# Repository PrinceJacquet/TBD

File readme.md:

# The dashboard of the car: TIM-07
* Software used 
    * KiCad v5
    * STM32 Cube IDE v1.3
    * Sublime Text

## Support Sheet for DashBoard development - TDB

### Function to code

* [x]  Led idle
    * [x] while(1) : blink Delay    
    * [x] PWM               

* [ ]  Led: inform on the status of the car__(hardware missing)__
    1. Break
    2. Front Headlight
    3. Back Headlight

* [ ]  CAN Bus Comminication
    - Rx
    - Tx
        
* [ ]  Servo Controller 
    * [x] PWM -- 50Hz  --> 1/20ms  *--untested*
    * [ ] (BASE) Timer to set the Cycle Duty (OFF / Slow incrementation or fast incrementation)
    * [ ] Timer to set the speed : The periode at which the cycle duty increment or decrement 
    * [x] Power the servo-motor ON/OFF

* [x]  Buttons and interruptions
    * Cycle to choose wiper speed
        * Wiper off
        * Wiper Speed 1
        * Wiper speed 2
    * Fan On/Off
    * Front Headlight 
    * Back Headlight
   
## On Hardware
* V1
    * CLIM switch 
    * Wiper push boutons
    * HeadLight Front
    * HeadLight Back
    * Break 
## How to:

### PWM 

- [link to course and tutorials!](https://visualgdb.com/tutorials/arm/stm32/pwm/)
- [link to ST resources on TIMERS](https://www.st.com/content/ccc/resource/training/technical/product_training/c4/1b/56/83/3a/a1/47/64/STM32L4_WDG_TIMERS_GPTIM.pdf/files/STM32L4_WDG_TIMERS_GPTIM.pdf/jcr:content/translations/en.STM32L4_WDG_TIMERS_GPTIM.pdf)
- [link to OpenClassroom course](https://openclassrooms.com/fr/courses/4117396-developpez-en-c-pour-lembarque/4629911-configurez-un-modulateur-de-longueur-d-impulsion)
- [link to Servo-Motor operating principle](https://howtomechatronics.com/how-it-works/how-servo-motors-work-how-to-control-servos-using-arduino/)
#### STM32 Timers HardWare
    * The hardwre is a bunch of separate block that can count from 0 to x
     And trigger events when the timer reach 0, maximum value or a compae value. 
#### What are the steps 
    1. We have to start the timer (so it can count)
        1. Pick the relevant timer and channel 
        2. Configure the following parameters so that the timer count at the frequency you need: T_timer=T_(clock)×prescaler×(autoreload+1)
            * counting mode up or down
            * set the prescaler (PSC)
            * set the period (ARR)
            * set clock division if any (CKD)
            * set repetition if any 
    2. We set the duty cycle
        * Using 
    3. We start the PWM using: HAL Functions from ST
    
### Interruptions 
    * Configure pin in STM32 CUBE MX as GPIO EXTIx
    * Using void EXTIx_y_IRQHandler(void){[[ }]]

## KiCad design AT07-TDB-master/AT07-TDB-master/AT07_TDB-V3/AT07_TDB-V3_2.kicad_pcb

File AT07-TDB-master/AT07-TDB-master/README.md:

# TDB Tim 07

### Fonctions necesseaires 
* Gestion EsGl
* Gestion "Clim"
* Pedale frein

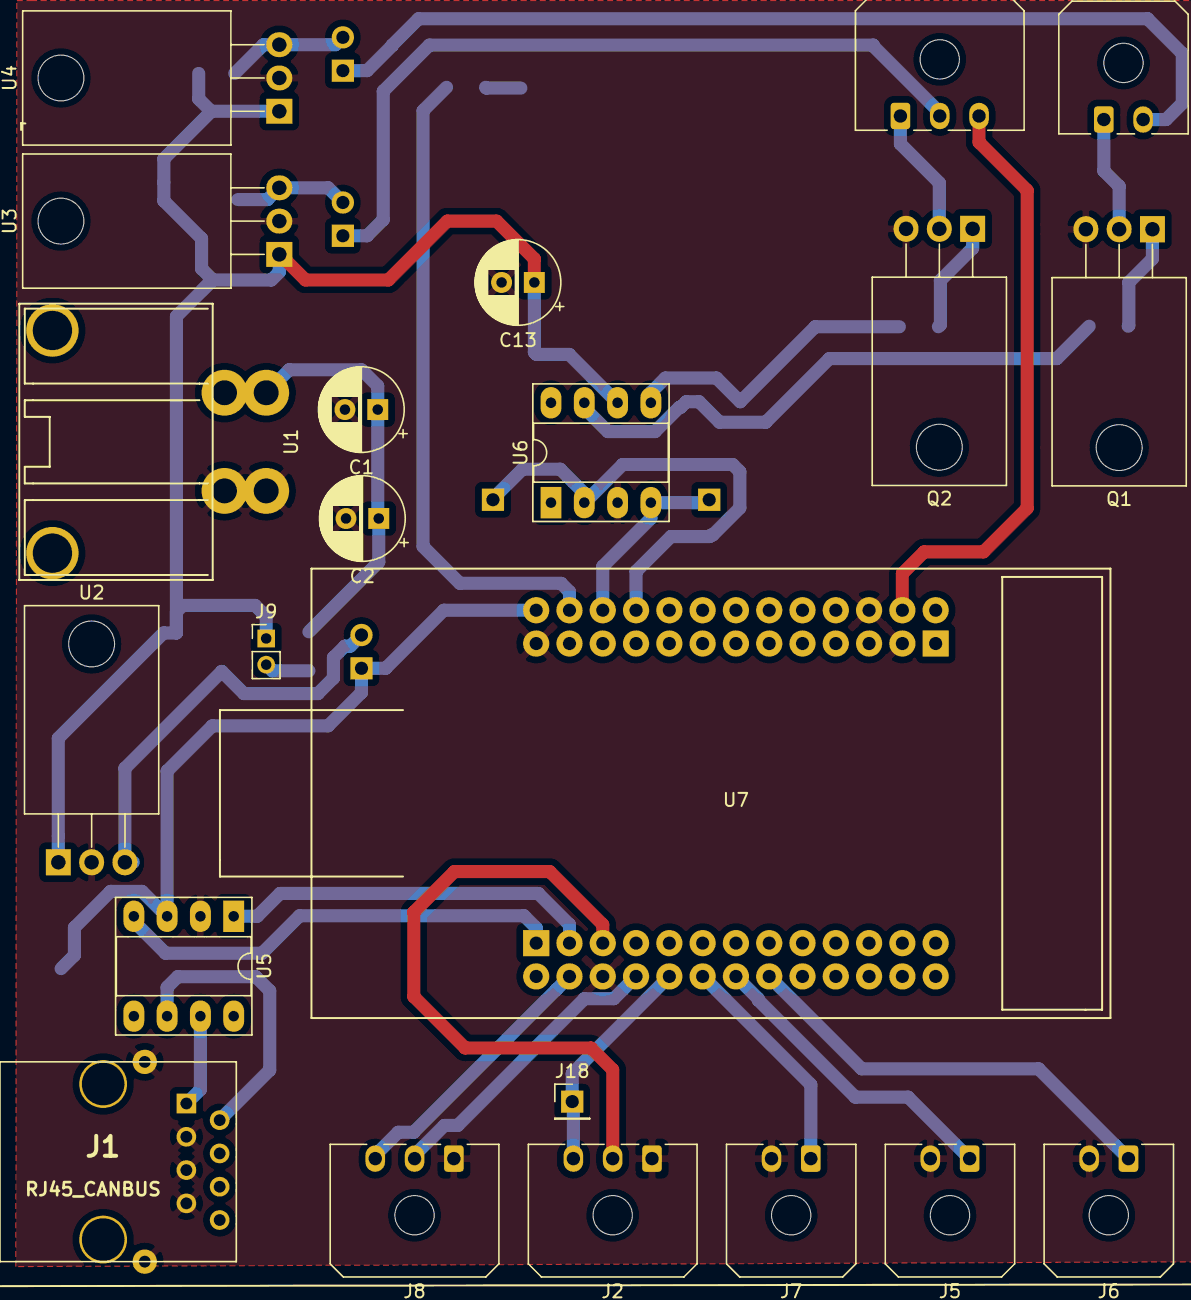
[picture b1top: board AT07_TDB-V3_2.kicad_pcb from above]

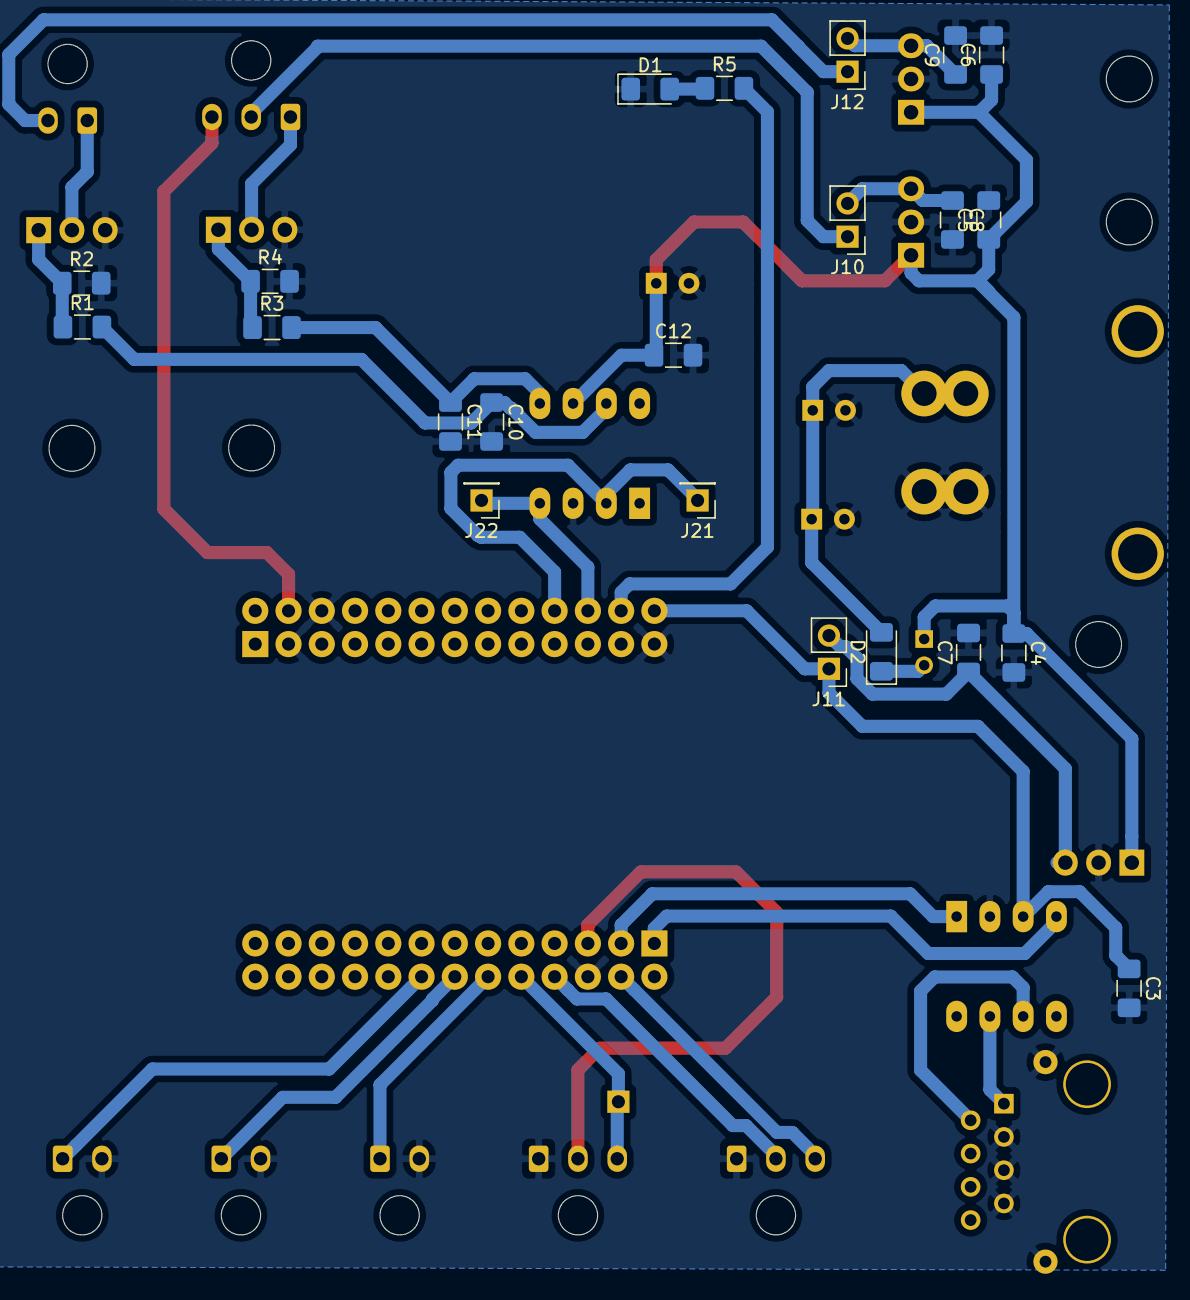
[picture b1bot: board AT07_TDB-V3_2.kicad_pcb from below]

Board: 2 copper layers, 44 parts (22 on the bottom side), 32 nets.

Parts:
C1: 22uF; CP_Radial_D6.3mm_P2.50mm
C2, C13: 1uF; CP_Radial_D6.3mm_P2.50mm
C3, C7, C8, C9, C12: 100nF; C_1206_3216Metric_Pad1.42x1.75mm_HandSolder
C4, C5, C6: 330nF; C_1206_3216Metric_Pad1.42x1.75mm_HandSolder
C10, C11: 1nF; C_1206_3216Metric_Pad1.42x1.75mm_HandSolder
D1: LED; D_1206_3216Metric_Pad1.42x1.75mm_HandSolder
D2: D; D_1206_3216Metric_Pad1.42x1.75mm_HandSolder
J1: RJ45_CANBUS; RJ45_CAN
J2: Conn_01x03_Female_Potar; Molex_Micro-Fit_3.0_43650-0300_1x03_P3.00mm_Horizontal
J3: Conn_01x03_Female_Servomotor; Molex_Micro-Fit_3.0_43650-0300_1x03_P3.00mm_Horizontal
J4, J5, J6, J7: Conn_01x02_Female; Molex_Micro-Fit_3.0_43650-0200_1x02_P3.00mm_Horizontal
J8: Conn_01x03_Female; Molex_Micro-Fit_3.0_43650-0300_1x03_P3.00mm_Horizontal
J9: Conn_01x02_Male; PinHeader_1x02_P2.00mm_Vertical
J10, J11, J12: Conn_01x02_Male; PinHeader_1x02_P2.54mm_Vertical
J18, J21, J22: Conn_01x01_Female; PinHeader_1x01_P2.54mm_Vertical
Q1, Q2: IRFZ44Z; TO-220-3_Horizontal_TabDown
R1, R3: 10; R_1206_3216Metric_Pad1.42x1.75mm_HandSolder
R2, R4: 10k; R_1206_3216Metric_Pad1.42x1.75mm_HandSolder
R5: R; R_1206_3216Metric_Pad1.42x1.75mm_HandSolder
U1: MOLEX_SABRE_46007-1102
U2, U3: L7805; TO-220-3_Horizontal_TabDown
U4: L7812; TO-220-3_Horizontal_TabDown
U5: MCP2551-I-SN; DIP-8_W7.62mm_Socket_LongPads
U6: TC4424; DIP-8_W7.62mm_Socket_LongPads
U7: STM32H103-OlimexBoard

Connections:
+3V3: J2.2, U7.5
+5V: C3.1, J11.1, U5.3, U7.52
+5VA: J3.2, J10.1
+12VA: J4.2, J12.1
+15V: C4.1, C5.1, C6.1, C12.1, C13.1, J9.1, U2.1, U3.1, U4.1, U6.6
BRAKES_SW: J7.1, U7.12
CANH: J1.1, U5.7
CANL: J1.2, U5.6
CANRX: U5.4, U7.1
CANTX: U5.1, U7.3
CLIM_CMD_HPWR: C10.1, R1.2, U6.7
CLIM_CMD_LPWR: J21.1, U6.2, U7.46
CLIM_SW: J5.1, U7.14
GND: C1.2, C2.2, C3.2, C4.2, C5.2, C6.2, C7.2, C8.2, C9.2, C10.2, C11.2, C12.2, C13.2, D1.1, J1.3, J1.5, J1.7, J1.9, J2.1, J5.2, J6.2, J7.2, J8.1, Q1.3, Q2.3, R2.2, R4.2, U1.1, U2.2, U3.2, U4.2, U5.2, U6.3, U7.6, U7.29, U7.32, U7.51
LIGHTS_SW: J6.1, U7.16
unnamed: C1.1, C2.1, D2.2, U1.2
unnamed: C7.1, J11.2, U2.3
unnamed: C8.1, J10.2, U3.3
unnamed: C9.1, J12.2, U4.3
unnamed: D1.2, R5.1
unnamed: D2.1, J9.2
unnamed: J3.1, Q2.2
unnamed: J4.1, Q1.2
unnamed: Q1.1, R1.1, R2.1
unnamed: Q2.1, R3.1, R4.1
unnamed: R5.2, U7.50
PWM_SERVO: J3.3, U7.30
SERVO_CMD_HPWR: C11.1, R3.2, U6.5
SERVO_CMD_LPWR: J22.1, U6.4, U7.48
SIGNAL_POTAR: J2.3, J18.1, U7.10
WIPER_SPEED_1: J8.2, U7.8
WIPER_SPEED_2: J8.3, U7.4

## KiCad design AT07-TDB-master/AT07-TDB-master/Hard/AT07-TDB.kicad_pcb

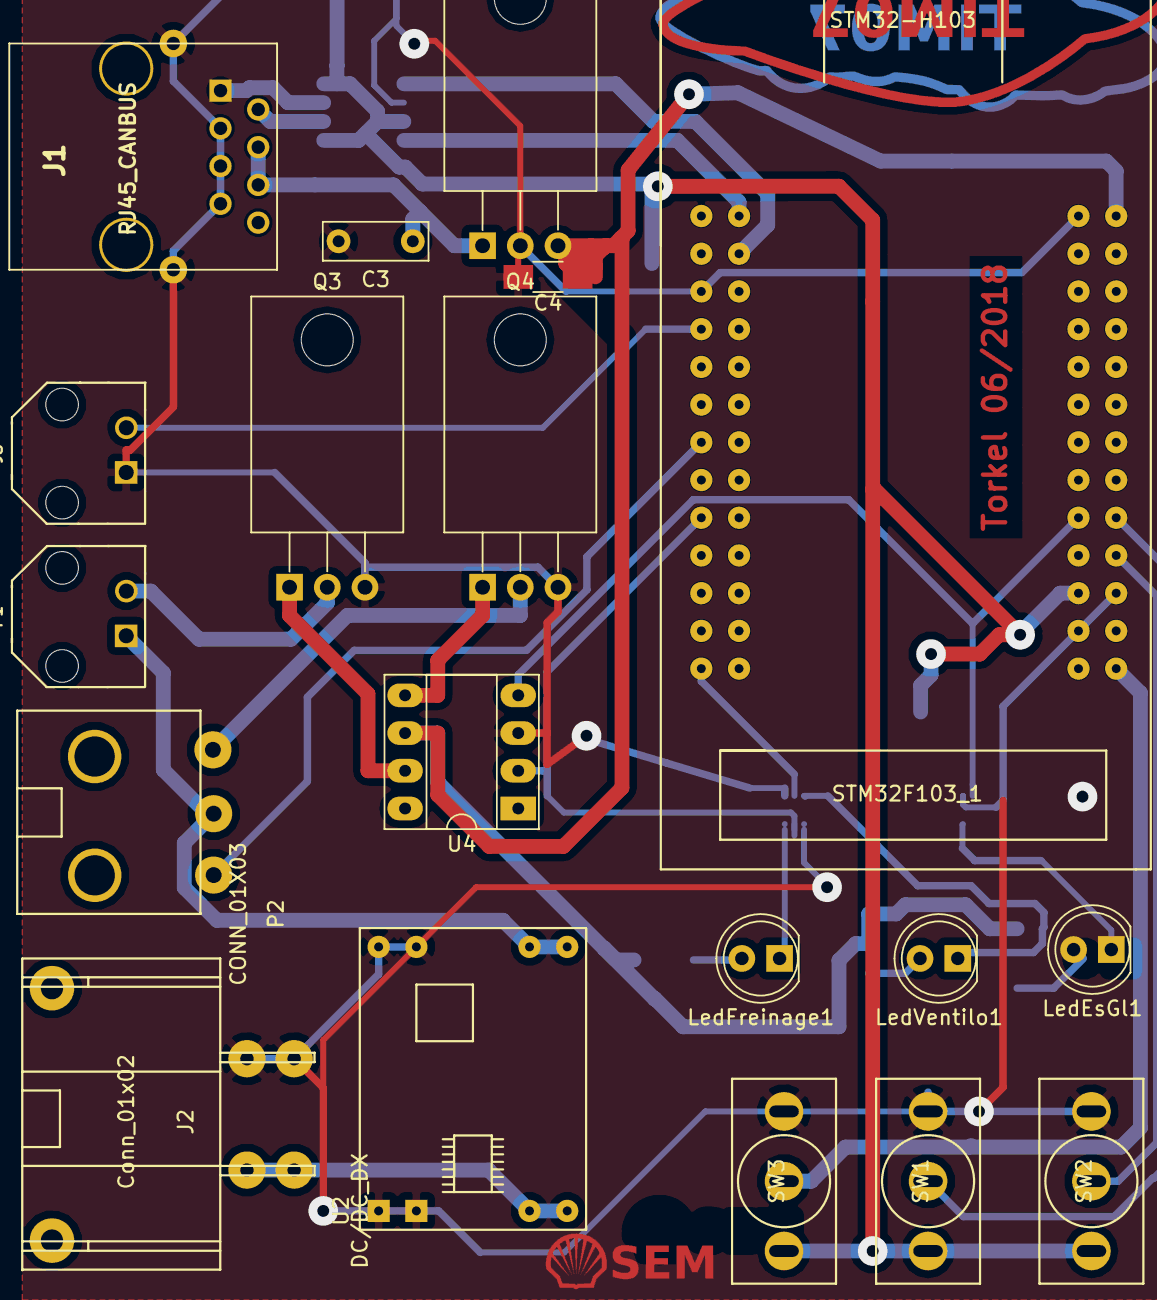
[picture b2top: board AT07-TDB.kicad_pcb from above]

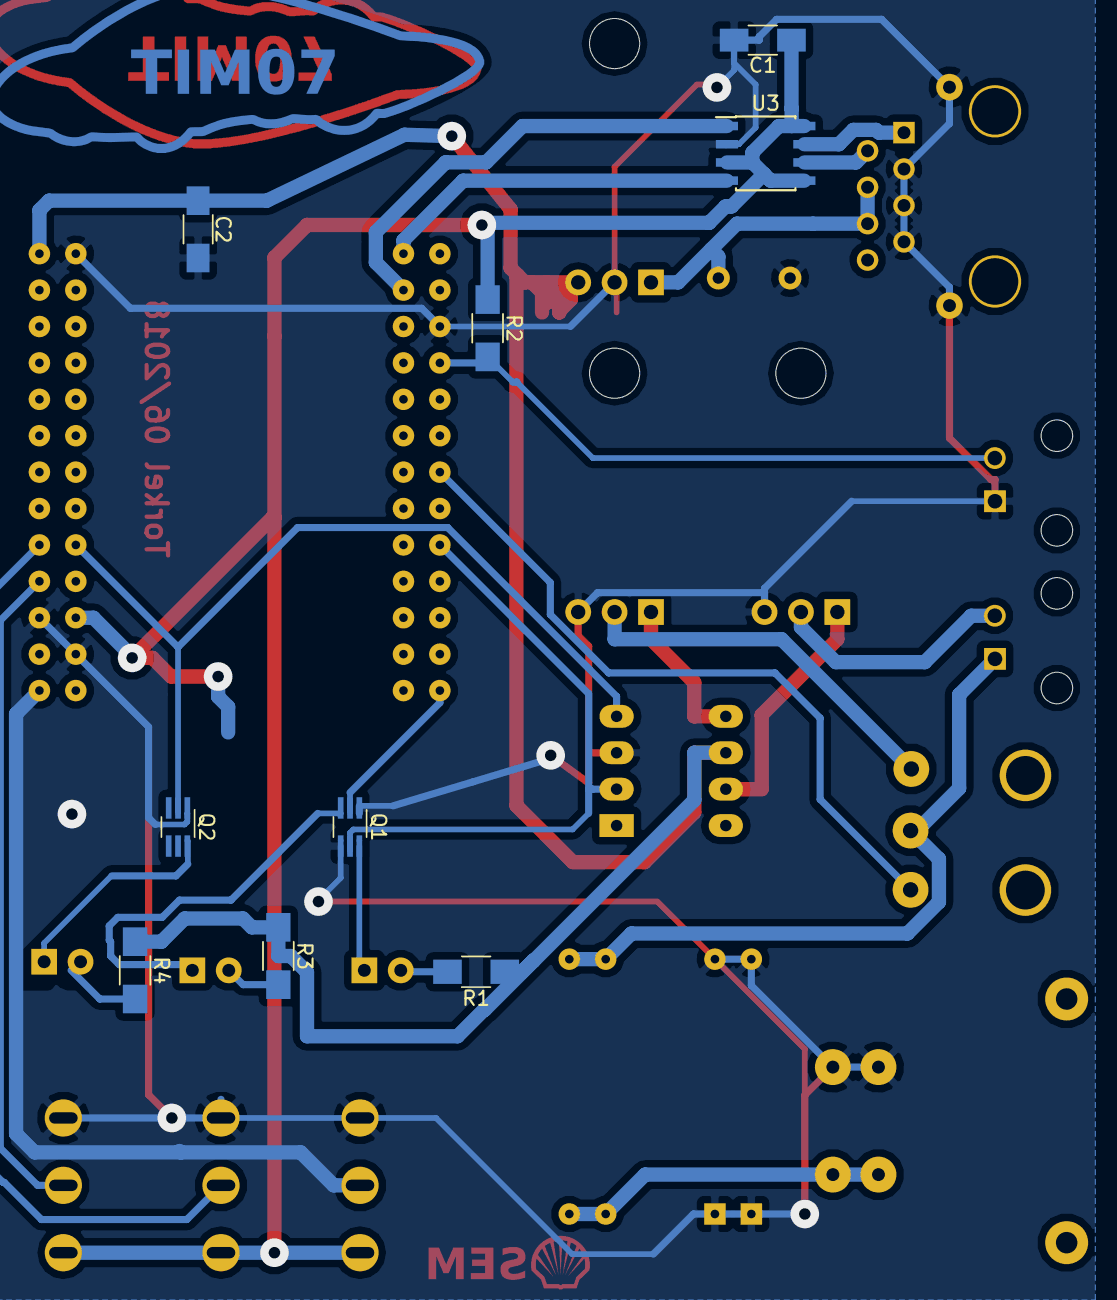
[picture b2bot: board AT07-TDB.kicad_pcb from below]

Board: 2 copper layers, 31 parts (9 on the bottom side), 28 nets.

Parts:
C1: C_Small; C_1206_HandSoldering
C2, C4: 100n; C_1206_HandSoldering
C3: 0.33u; C_Disc_D7.0mm_W2.5mm_P5.00mm
J1: RJ45_CANBUS; RJ45_CAN
J2: Conn_01x02; CON_SERIE_SABRE_2
J3: Conn_01x02; Micro-Fit_2_Coude
LedEsGl1: LED; LED_D5.0mm
LedFreinage1: LED; LED_D5.0mm
LedVentilo1: LED; LED_D5.0mm
P1: Connecteur Ventilo; Micro-Fit_2_Coude
P2: CONN_01X03; MINIFIT-JR
Q1, Q2: FDG1024NZ; SOT-363_SC-70-6_Handsoldering
Q3, Q4: Q_NMOS_GDS; TO-220_Horizontal
R1, R3, R4: 400; R_1206_HandSoldering
R2: 2.7k; R_1206_HandSoldering
STM32F103_1: STM32-H103; STM32-H103_Emp
SW1, SW2, SW3: SW_SPDT; Switch_Stick_SPDT
U1: L7805; TO-220_Horizontal
U2: DC/DC_DX; DCDC_DX_SMALL
U3: SN65HVD230; SOIC-8_3.9x4.9mm_Pitch1.27mm
U4: TC4424; DIP-8_W7.62mm_Socket_LongPads
VAL: REF; logo_tim07_large_top
VAL#2: REF; logo_tim07_large_bottom
VAL#3: REF; logo_shell2_small_top

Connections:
+3V3: C1.1, R2.1, STM32F103_1.31, SW1.3, SW2.3, SW3.3, U3.3, U3.5, U3.8
+5V: C2.1, C4.1, R1.1, R3.1, R4.1, STM32F103_1.52, U1.3, U4.6
+5VP: P1.1, P2.2, U2.3
+9V: C3.1, J1.4, J1.6, U1.1
+15V: J2.2, U2.1
EsGlbutton: STM32F103_1.34, SW2.2
GND: C1.2, C2.2, C3.2, C4.2, J1.3, J1.5, J1.7, J1.9, J2.1, J3.1, Q1.1, Q1.4, Q2.1, Q3.3, Q4.3, STM32F103_1.6, STM32F103_1.29, STM32F103_1.32, STM32F103_1.51, SW1.1, SW2.1, SW3.1, U1.2, U2.2, U2.4, U3.2, U4.3
LedFreinage: Q1.2, STM32F103_1.26
Lightbutton: STM32F103_1.28, SW3.2
unnamed: J1.1, U3.7
unnamed: J1.2, U3.6
unnamed: LedEsGl1.1, Q2.6
unnamed: LedEsGl1.2, R4.2
unnamed: LedFreinage1.1, Q1.6
unnamed: LedFreinage1.2, R1.2
unnamed: LedVentilo1.1, Q1.3
unnamed: LedVentilo1.2, R3.2
unnamed: P1.2, Q3.2
unnamed: P2.3, Q4.2
unnamed: Q3.1, U4.7
unnamed: Q4.1, U4.5
unnamed: STM32F103_1.1, U3.4
unnamed: STM32F103_1.3, U3.1
Pedalebutton: J3.2, R2.2, STM32F103_1.8
Servo_Enable: Q2.2, STM32F103_1.35, U4.4
Servo_PWM: P2.1, STM32F103_1.14
Ventilo_Enable: Q1.5, STM32F103_1.18, U4.2
Ventilobutton: STM32F103_1.36, SW1.2

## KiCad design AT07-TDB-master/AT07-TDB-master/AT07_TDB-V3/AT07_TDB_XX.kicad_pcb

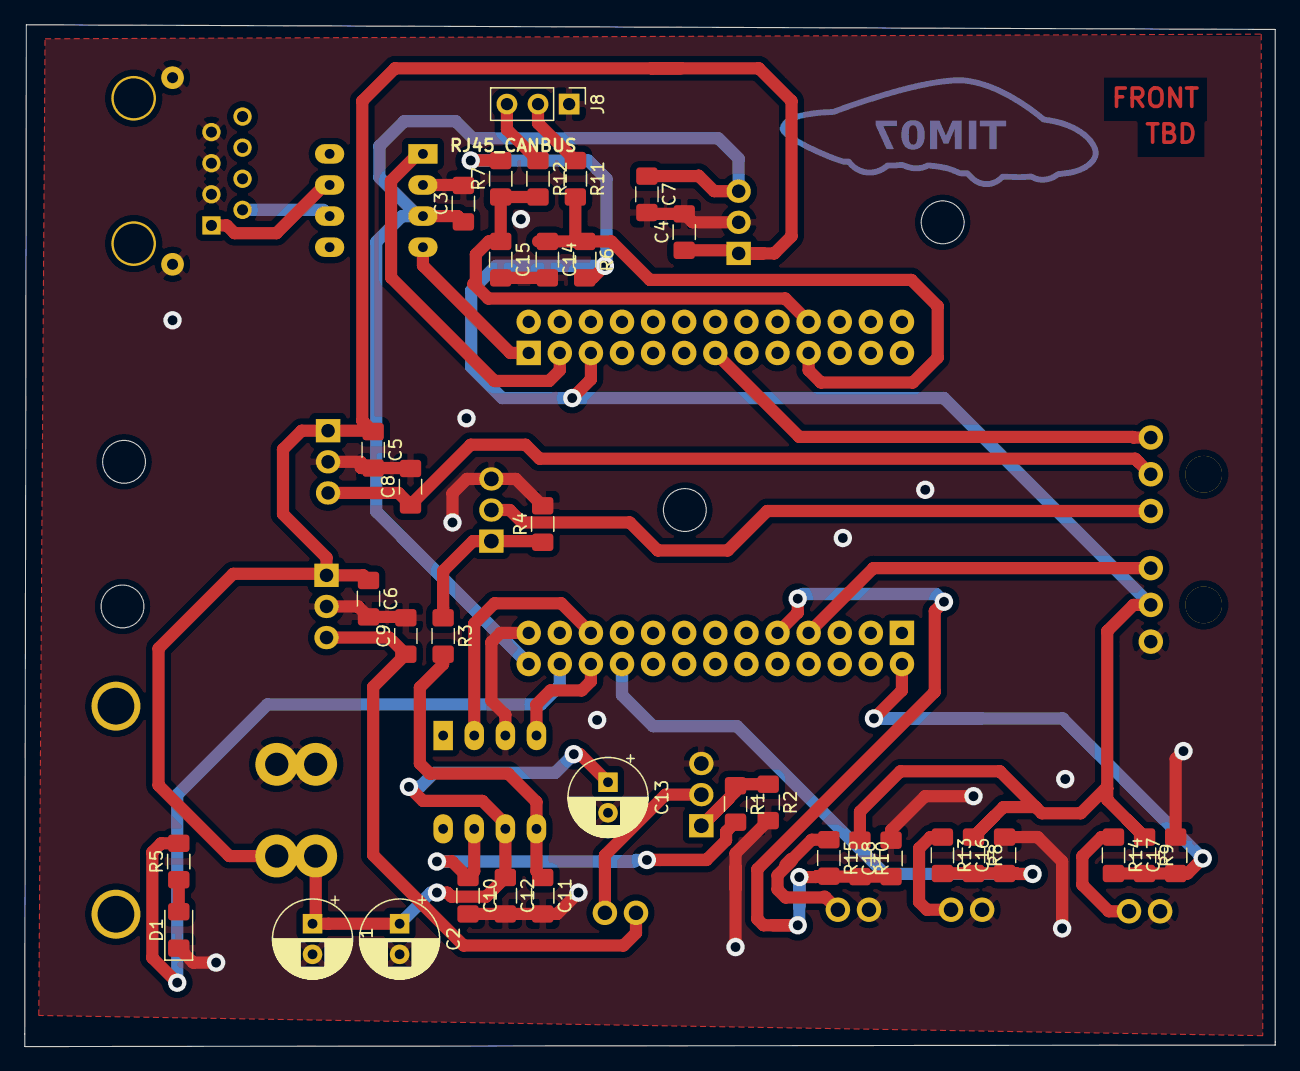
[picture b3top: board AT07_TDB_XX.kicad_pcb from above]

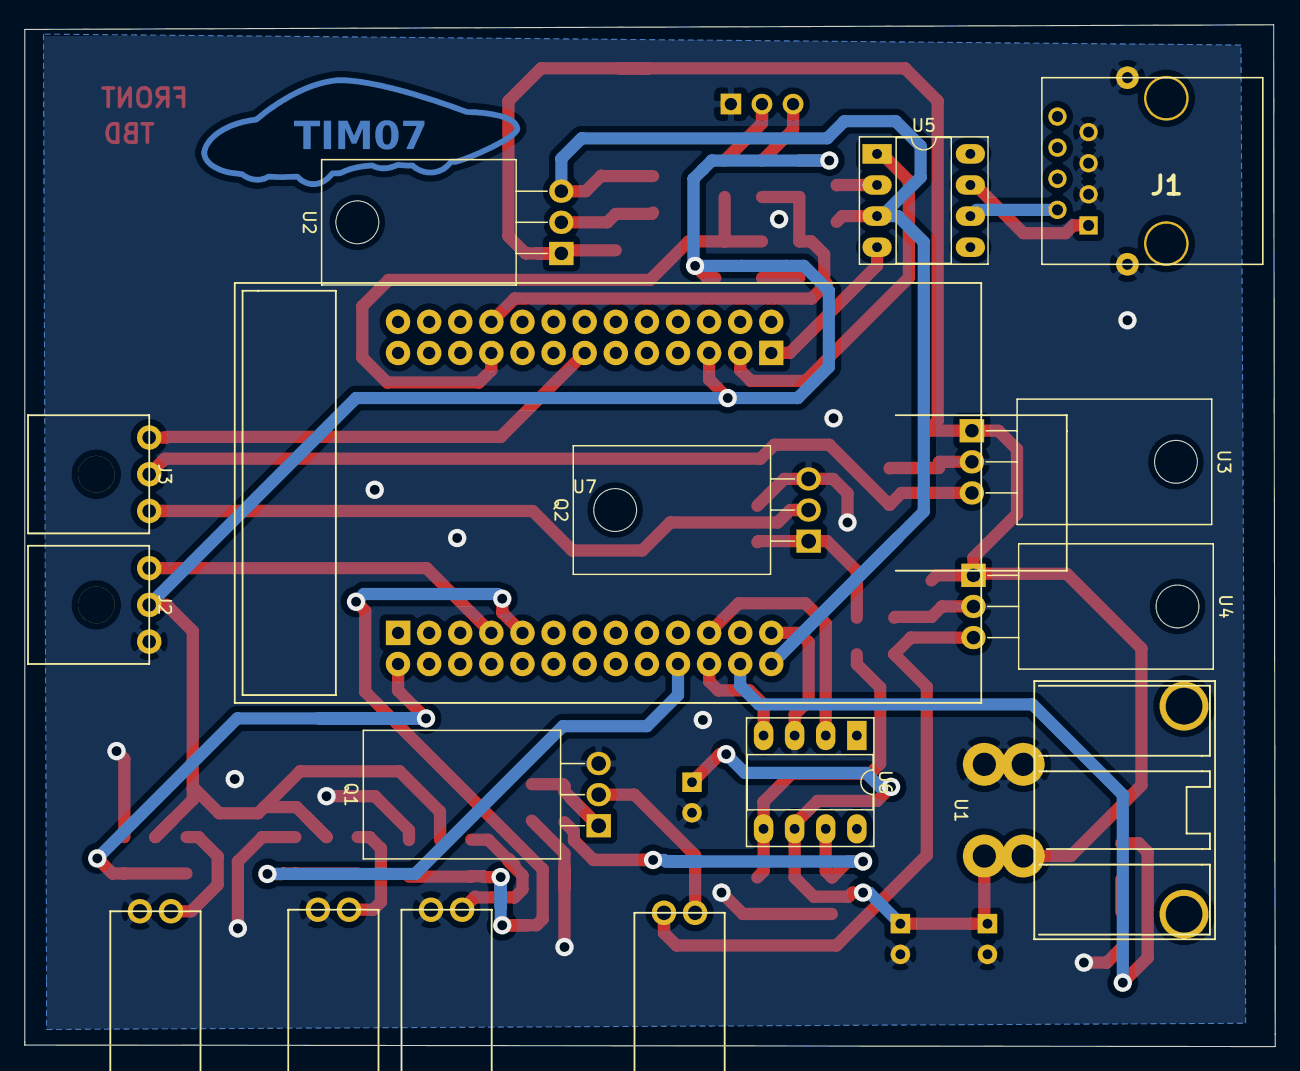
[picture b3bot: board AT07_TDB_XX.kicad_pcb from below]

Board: 2 copper layers, 102.1 x 83.4 mm, 52 parts (16 on the bottom side), 32 nets.

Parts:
C1: 22uF; CP_Radial_D6.3mm_P2.50mm
C2, C13: 1uF; CP_Radial_D6.3mm_P2.50mm
C3, C7, C8, C9, C12, C14, C15, C16, C17, C18: 100nF; C_1206_3216Metric_Pad1.42x1.75mm_HandSolder
C4, C5, C6: 330nF; C_1206_3216Metric_Pad1.42x1.75mm_HandSolder
C10, C11: 1nF; C_1206_3216Metric_Pad1.42x1.75mm_HandSolder
D1: LED; D_1206_3216Metric_Pad1.42x1.75mm_HandSolder
J1: RJ45_CANBUS; RJ45_CAN
J2: Conn_01x03_Female_Potar; Molex_Micro-Fit_3.0_3pos
J3: Conn_01x03_Female_Servomotor; Molex_Micro-Fit_3.0_3pos
J4, J5, J6, J7: Conn_01x02_Female; MOLEX_70553-0001
J8: Conn_01x03_Female; PinHeader_1x03_P2.54mm_Vertical
Q1, Q2: IRFZ44Z; TO-220F-3_Horizontal_TabDown
R1, R3: 10; R_1206_3216Metric_Pad1.42x1.75mm_HandSolder
R2, R4: 10k; R_1206_3216Metric_Pad1.42x1.75mm_HandSolder
R5: R; R_1206_3216Metric_Pad1.42x1.75mm_HandSolder
R6, R7, R8, R9, R10: 33k; R_1206_3216Metric_Pad1.42x1.75mm_HandSolder
R11, R12, R13, R14, R15: 1k; R_1206_3216Metric_Pad1.42x1.75mm_HandSolder
U1: MOLEX_SABRE_46007-1102
U2, U3: L7805; TO-220-3_Horizontal_TabDown
U4: L7812; TO-220-3_Horizontal_TabDown
U5: MCP2551-I-SN; DIP-8_W7.62mm_Socket_LongPads
U6: TC4424; DIP-8_W7.62mm_Socket_LongPads
U7: STM32H103-OlimexBoard
VAL: REF; logo_tim07_medium_bottom

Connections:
+3V3: J2.2, R6.2, R7.2, R8.1, R9.1, R10.1, U7.5
+5V: C3.1, C7.1, U2.3, U5.3, U7.52
+5VA: C8.1, J3.2, U3.3
+12VA: C9.1, J4.2, U4.3
+15V: C1.1, C2.1, C4.1, C5.1, C6.1, C12.1, C13.1, U1.2, U2.1, U3.1, U4.1, U6.6
BRAKES_SW: C18.1, R10.2, R15.2, U7.35
CANH: J1.1, U5.7
CANL: J1.2, U5.6
CANRX: U5.4, U7.1
CANTX: U5.1, U7.3
CLIM_CMD_HPWR: C10.1, R1.2, U6.7
CLIM_CMD_LPWR: U6.2, U7.47
CLIM_SW: C16.1, R8.2, R13.2, U7.46
GND: C1.2, C2.2, C3.2, C4.2, C5.2, C6.2, C7.2, C8.2, C9.2, C10.2, C11.2, C12.2, C13.2, C14.2, C15.2, C16.2, C17.2, C18.2, D1.1, J1.3, J1.5, J1.7, J1.9, J2.1, J5.2, J6.2, J7.2, J8.1, Q1.3, Q2.3, R2.2, R4.2, U1.1, U2.2, U3.2, U4.2, U5.2, U6.3, U7.6, U7.29, U7.32, U7.51
LIGHTS_SW: C17.1, R9.2, R14.2, U7.28
unnamed: D1.2, R5.1
unnamed: J3.1, Q2.2
unnamed: J4.1, Q1.2
unnamed: J5.1, R13.1
unnamed: J6.1, R14.1
unnamed: J7.1, R15.1
unnamed: J8.2, R11.1
unnamed: J8.3, R12.1
unnamed: Q1.1, R1.1, R2.1
unnamed: Q2.1, R3.1, R4.1
unnamed: R5.2, U7.50
PWM_SERVO: J3.3, U7.13
SERVO_CMD_HPWR: C11.1, R3.2, U6.5
SERVO_CMD_LPWR: U6.4, U7.48
SIGNAL_POTAR: J2.3, U7.33
WIPER_SPEED_1: C14.1, R6.1, R11.2, U7.19
WIPER_SPEED_2: C15.1, R7.1, R12.2, U7.20

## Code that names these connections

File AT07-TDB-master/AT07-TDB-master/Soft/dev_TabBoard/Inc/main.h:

/* USER CODE BEGIN Header */
/**
  ******************************************************************************
  * @file           : main.h
  * @brief          : Header for main.c file.
  *                   This file contains the common defines of the application.
  ******************************************************************************
  * @attention
  *
  * <h2><center>&copy; Copyright (c) 2019 STMicroelectronics.
  * All rights reserved.</center></h2>
  *
  * This software component is licensed by ST under BSD 3-Clause license,
  * the "License"; You may not use this file except in compliance with the
  * License. You may obtain a copy of the License at:
  *                        opensource.org/licenses/BSD-3-Clause
  *
  ******************************************************************************
  */
/* USER CODE END Header */

/* Define to prevent recursive inclusion -------------------------------------*/
#ifndef __MAIN_H
#define __MAIN_H

#ifdef __cplusplus
extern "C" {
#endif

/* Includes ------------------------------------------------------------------*/
#include "stm32f1xx_hal.h"

/* Private includes ----------------------------------------------------------*/
/* USER CODE BEGIN Includes */

/* USER CODE END Includes */

/* Exported types ------------------------------------------------------------*/
/* USER CODE BEGIN ET */

/* USER CODE END ET */

/* Exported constants --------------------------------------------------------*/
/* USER CODE BEGIN EC */

/* USER CODE END EC */

/* Exported macro ------------------------------------------------------------*/
/* USER CODE BEGIN EM */

/* USER CODE END EM */

/* Exported functions prototypes ---------------------------------------------*/
void Error_Handler(void);

/* USER CODE BEGIN EFP */

/* USER CODE END EFP */

/* Private defines -----------------------------------------------------------*/
#define CLIM_CMD_LPWR_Pin GPIO_PIN_13
#define CLIM_CMD_LPWR_GPIO_Port GPIOC
#define WIPER_SPEED_2_Pin GPIO_PIN_4
#define WIPER_SPEED_2_GPIO_Port GPIOC
#define SERVO_CMD_LPWR_Pin GPIO_PIN_1
#define SERVO_CMD_LPWR_GPIO_Port GPIOB
#define WIPER_SPEED_1_Pin GPIO_PIN_10
#define WIPER_SPEED_1_GPIO_Port GPIOB
#define CLIM_SW_Pin GPIO_PIN_13
#define CLIM_SW_GPIO_Port GPIOB
#define BRAKES_SW_Pin GPIO_PIN_14
#define BRAKES_SW_GPIO_Port GPIOB
#define LIGHTS_SW_Pin GPIO_PIN_6
#define LIGHTS_SW_GPIO_Port GPIOC
#define SIGNAL_POTAR_Pin GPIO_PIN_8
#define SIGNAL_POTAR_GPIO_Port GPIOC
#define LED_Pin GPIO_PIN_9
#define LED_GPIO_Port GPIOC
/* USER CODE BEGIN Private defines */

/* USER CODE END Private defines */

#ifdef __cplusplus
}
#endif

#endif /* __MAIN_H */

/************************ (C) COPYRIGHT STMicroelectronics *****END OF FILE****/

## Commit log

2020-05-29 Backlink to CADLAB.io has been added.
2020-05-29 base
2020-06-17 Re-master workstation : Put every relatade files together
2020-06-17 Change readme from txt to md
2020-06-17 End of workstation setup + Blink (Delay) ^^
2020-06-18 untested PWM + updated ReadMe (added link and howto)
2020-06-20 Tested PWM, added Interuptions, define new macro for led idle
2020-06-23 Added, controled and tested base PWM of the Servo-motor Better used of #define and macro ...still waiting to setup the CAN (and test it) ...still waiting on fixing speed instead of position for the s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
2020-06-23 add supported software to use/see/modify the files
2020-06-26 Added new file for wiper
2020-06-27 TIM 1 not firing on updtae or overflow ?! I amybe shouldnt merge not working files..but who cares ? ^^
2020-06-27 TIM1 inturrupt working
2020-07-09 commit after hard disk reset
2020-07-27 Beta version. all functions are working and are tested. - break (CAN msg on rise and fall) - wiper control - fan - Front light and back light the code still need to be organize and commented.
2020-08-01 commit to the newwww branch
